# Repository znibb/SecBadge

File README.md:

View this project on [CADLAB.io](https://cadlab.io/node/992). 

# SecBadge

Board dimensions: 69x43 mm

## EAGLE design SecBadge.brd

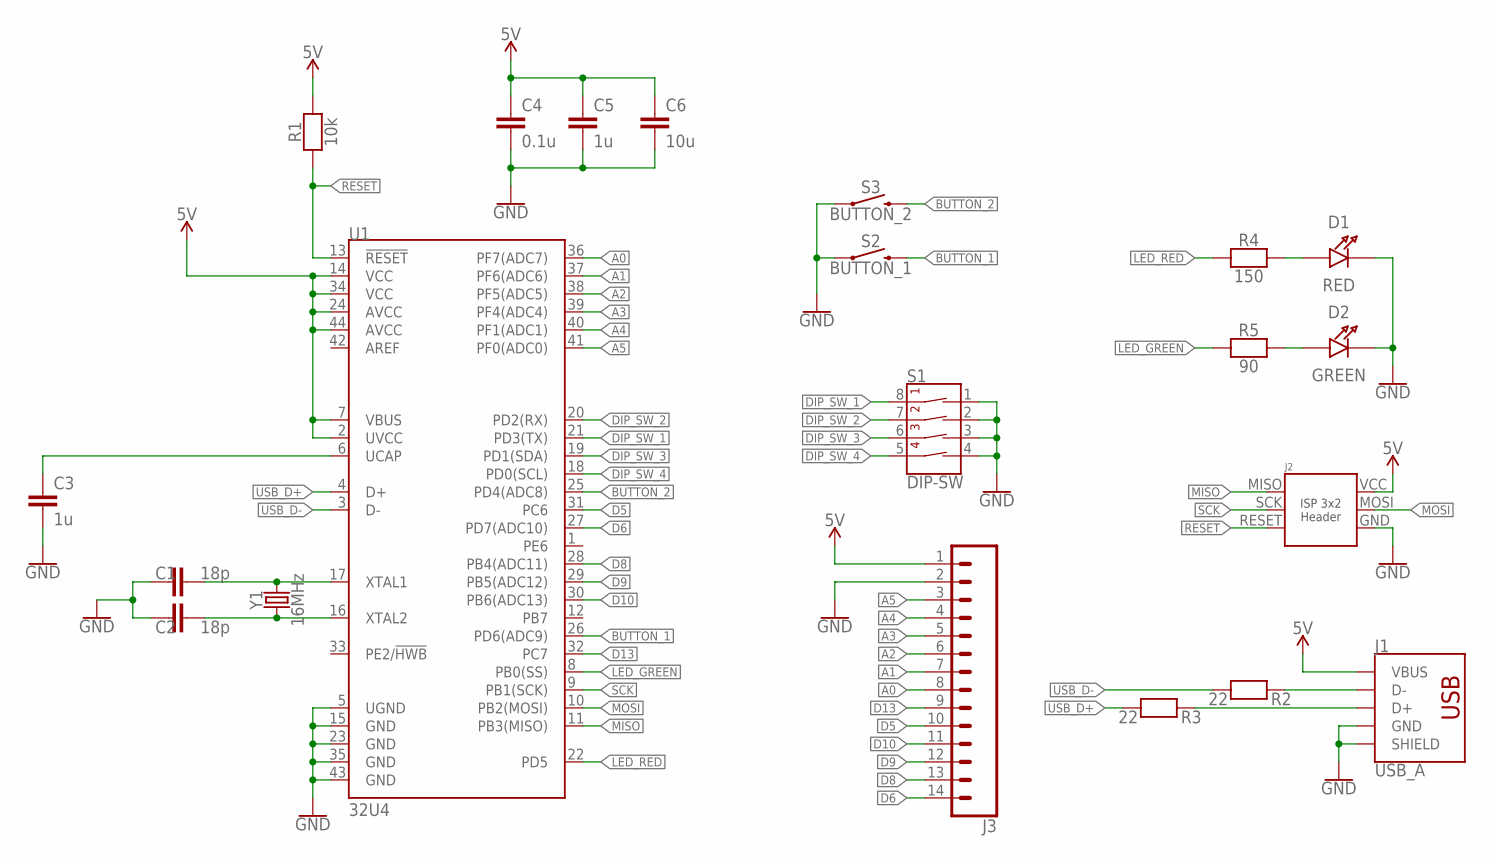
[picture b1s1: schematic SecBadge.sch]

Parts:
C1, C2: 18p; 1206
C3, C5: 1u; 1206
C4: 0.1u; 1206
C6: 10u; 1206
D1: RED; LED-1206
D2: GREEN; LED-1206
J1: USB_A; USB_A_MALE_THT
J2: AVR_ISP_PROG_3X2; 3X2_NO_SILK
J3: CONN_14; 1X14
R1: 10k; 1206
R2, R3: 22; 1206
R4: 150; 1206
R5: 90; 1206
S1: DIP-SW; DIP8
S2: BUTTON_1; TACTILE_SWITCH_PTH_6.0MM
S3: BUTTON_2; TACTILE_SWITCH_PTH_6.0MM
U1: 32U4; TQFP44
Y1: 16MHz; HC49UP

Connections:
5V: C4.1, C5.1, C6.1, J1.VBUS, J2.VCC, J3.1, R1.1, U1.2 (UVCC), U1.7 (VBUS), U1.14 (VCC), U1.24 (AVCC), U1.34 (VCC), U1.44 (AVCC)
A0: J3.8, U1.36 (PF7(ADC7))
A1: J3.7, U1.37 (PF6(ADC6))
A2: J3.6, U1.38 (PF5(ADC5))
A3: J3.5, U1.39 (PF4(ADC4))
A4: J3.4, U1.40 (PF1(ADC1))
A5: J3.3, U1.41 (PF0(ADC0))
BUTTON_1: S2.3 (2), U1.26 (PD6(ADC9))
BUTTON_2: S3.3 (2), U1.25 (PD4(ADC8))
D5: J3.10, U1.31 (PC6)
D6: J3.14, U1.27 (PD7(ADC10))
D8: J3.13, U1.28 (PB4(ADC11))
D9: J3.12, U1.29 (PB5(ADC12))
D10: J3.11, U1.30 (PB6(ADC13))
D13: J3.9, U1.32 (PC7)
DIP_SW_1: S1.8 (1B), U1.21 (PD3(TX))
DIP_SW_2: S1.7 (2B), U1.20 (PD2(RX))
DIP_SW_3: S1.6 (3B), U1.19 (PD1(SDA))
DIP_SW_4: S1.5 (4B), U1.18 (PD0(SCL))
GND: C1.1, C2.1, C3.2, C4.2, C5.2, C6.2, D1.C (CATHODE), D2.C (CATHODE), J1.GND, J1.SHIELD1 (SHIELD), J1.SHIELD2 (SHIELD), J2.GND, J3.2, S1.1 (1A), S1.2 (2A), S1.3 (3A), S1.4 (4A), S2.1, S3.1, U1.5 (UGND), U1.15 (GND), U1.23 (GND), U1.35 (GND), U1.43 (GND)
LED_GREEN: R5.2, U1.8 (PB0(SS))
LED_RED: R4.2, U1.22 (PD5)
MISO: J2.MISO, U1.11 (PB3(MISO))
MOSI: J2.MOSI, U1.10 (PB2(MOSI))
unnamed: C1.2, U1.17 (XTAL1), Y1.2
unnamed: J1.D-, R2.2
unnamed: J1.D+, R3.2
unnamed: C2.2, U1.16 (XTAL2), Y1.1
unnamed: C3.1, U1.6 (UCAP)
unnamed: D1.A (ANODE), R4.1
unnamed: D2.A (ANODE), R5.1
RESET: J2.RESET, R1.2, U1.13 (!RESET)
SCK: J2.SCK, U1.9 (PB1(SCK))
USB_D+: R3.1, U1.4 (D+)
USB_D-: R2.1, U1.3 (D-)

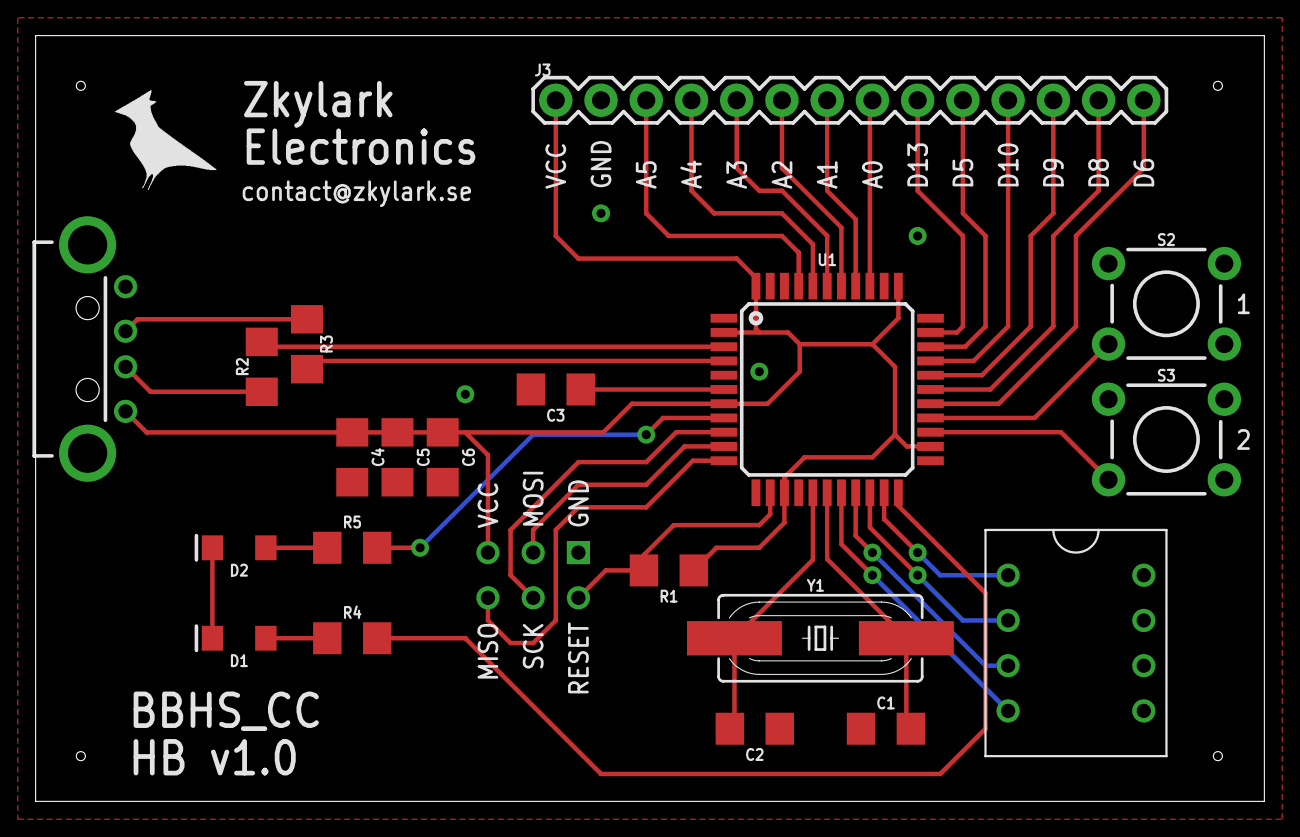
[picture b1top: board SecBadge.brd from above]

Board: 2 copper layers, 69.0 x 43.0 mm, 21 parts (0 on the bottom side), 35 nets.

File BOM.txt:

Partlist exported from C:/Users/znibb/Dropbox/Eagle_7.6/projects/SecBadge/SecBadge.sch at 01/04/2018 13:42

Part Value  Device                          Package                  Description          PROD_ID     SF_SKU    VALUE
C1   18p    CAPACITOR1206                   1206                                                                     
C2   18p    CAPACITOR1206                   1206                                                                     
C3   1u     CAPACITOR1206                   1206                                                                     
C4   0.1u   CAPACITOR1206                   1206                                                                     
C5   1u     CAPACITOR1206                   1206                                                                     
C6   10u    CAPACITOR1206                   1206                                                                     
D1   RED    LED                             LED-1206                                                                 
D2   GREEN  LED                             LED-1206                                                                 
J1   USB_A  USB_A                           USB_A_MALE_THT           USB-A Connector                                 
J2          AVR_ISP_PROG_3X2                3X2_NO_SILK              ISP Header                                      
R1   10k    RESISTOR1206                    1206                                                                     
R2   22     RESISTOR1206                    1206                                                                     
R3   22     RESISTOR1206                    1206                                                                     
R4   150    RESISTOR1206                    1206                                                                     
R5   90     RESISTOR1206                    1206                                                                     
S1   DIP-SW DIP-SW-4POSPHT                  DIP8                     4-Position DIP Switc                            
S2          MOMENTARY-SWITCH-SPST-PTH-6.0MM TACTILE_SWITCH_PTH_6.0MM Momentary Switch (Pu  SWCH-08441 COM-00097      
S3          MOMENTARY-SWITCH-SPST-PTH-6.0MM TACTILE_SWITCH_PTH_6.0MM Momentary Switch (Pu  SWCH-08441 COM-00097      
U1   32U4   ATMEGA32U4TQFP-44               TQFP44                   Atmel MCU, 32KByte   IC-11161              32U4 
Y1   16MHz  CRYSTALSMD-HC49UP               HC49UP                   Crystals (Generic)

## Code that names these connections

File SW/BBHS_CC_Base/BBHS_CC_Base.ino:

/*
Base sketch for the Bug Bounty Hunters Sweden Challenge Card.
Button 1 turns on the green LED for a set amount of time, DIP1&2 doubles the on-time respectively.
Button 2 turns on the red LED for a set amount of time, DIP3&4 doubles the on-time respectively.

Known issue: Clock rollover after 49 days runtime will make LEDs turn on "for good", deal with it.
*/

// DIP switches: 1-PD3, 2-PD2, 3-PD1, 4-PD0
// Buttons: 1-PD6-D12, 2-PD4-D4
// LEDs: Green-PB0, Red-PD5

// For explanation of port manipulation see: https://www.arduino.cc/en/Reference/PortManipulation

#include <Bounce2.h>  // Used for bounce-free buttons

// Bit masks for each feature
#define DIP1 B00001000
#define DIP2 B00000100
#define DIP3 B00000010
#define DIP4 B00000001
#define BUTTON1 B01000000
#define BUTTON2 B00010000
#define LED_GREEN B00000001
#define LED_RED B00100000

// Debouncer objects
Bounce bouncer1 = Bounce();
Bounce bouncer2 = Bounce();

// Function declarations
bool getButton(byte);
bool getDIP(byte);
void setLED(byte, bool);

// Parameters
const byte debounceInterval = 20;
const int baseLedOnTime = 1000;

// Variables
bool ledGreenState = false;
bool ledRedState = false;
unsigned long ledGreenOffTime = 0;
unsigned long ledRedOffTime = 0;

void setup() {  
  // DIP switches
  DDRD &=  ~(DIP1 | DIP2 | DIP3 | DIP4);  // Set as inputs
  PORTD |=  (DIP1 | DIP2 | DIP3 | DIP4);  // Activate input pullups

  // Buttons
  DDRD &=  ~(BUTTON1 | BUTTON2);        // Set Button 1&2 as inputs
  PORTD |=  (BUTTON1 | BUTTON2);        // Activate input pullups
  bouncer1.attach(12);                  // Attach debouncer to button 1
  bouncer1.interval(debounceInterval);  // Set debounce deadzone
  bouncer2.attach(4);                   // Attach debouncer to button 2
  bouncer2.interval(debounceInterval);  // Set debounce deadzone

  // LEDs
  DDRB |=   LED_GREEN;  // Set Green LED as output
  PORTB &= ~LED_GREEN;  // Set Green LED default low
  DDRD |=   LED_RED;    // Set Red LED as output
  PORTD &= ~LED_RED;    // Set Red LED default low
}

void loop() {
  // Update bouncers
  bouncer1.update();
  bouncer2.update();
  
  // If button 1 was pressed, turn on green LED
  if(bouncer1.fell() == HIGH){
    setLED(1, HIGH);
    ledGreenState = true;
    int duration = baseLedOnTime;

    // Double the LED on time for each of DIP1&2 that is ON (bit shift left <=> multiply by 2)
    if(getDIP(1) == LOW){
      duration = duration << 1;
    }
    if(getDIP(2) == LOW){
      duration =  duration << 1;
    }

    // Set planned time to turn off
    ledGreenOffTime = millis() + duration;    
  }

  // If button 2 was pressed, turn on red LED
  if(bouncer2.fell() == HIGH){
    setLED(2, HIGH);
    ledRedState = true;
    int duration = baseLedOnTime;

    // Double the LED on time for each of DIP3&4 that is ON (bit shift left <=> multiply by 2)
    if(getDIP(3) == LOW){
      duration = duration << 1;
    }
    if(getDIP(4) == LOW){
      duration =  duration << 1;
    }

    // Set planned time to turn off
    ledRedOffTime = millis() + duration;    
  }

  // Check if LEDs are due to turn off
  if(ledGreenState){  // If Green LED is lit
    if(millis() >= ledGreenOffTime){
      setLED(1, false);
      ledGreenState = false;
    }
  }
  if(ledRedState){  // If Red LED is lit
    if(millis() >= ledRedOffTime){
      setLED(2, false);
      ledRedState = false;
    }
  }
}

// Returns the state of buttons 1 and 2, LOW = button pressed
bool getButton(byte i){
  switch(i){
    case 1:
      return PIND &= BUTTON1;
    case 2:
      return PIND &= BUTTON2;
    default:
      return false;
  }
}

// Returns the state of DIP switch 1-4, LOW = ON
bool getDIP(byte i){
  switch(i){
    case 1:
      return PIND &= DIP1;
    case 2:
      return PIND &= DIP2;
    case 3:
      return PIND &= DIP3;
    case 4:
      return PIND &= DIP4;
    default:
      return false;
  }
}

// Sets the state of LED 1&2 (green&red), HIGH = ON
void setLED(byte i, bool value){
  switch(i){
    case 1: // Green LED
      if(value == HIGH){
        PORTB |= LED_GREEN;
      }
      else {
        PORTB &= ~LED_GREEN;
      }
      break;
    case 2: // Red LED
      if(value == HIGH){
        PORTD |= LED_RED;
      }
      else{
        PORTD &= ~LED_RED;
      }
      break;
    default:
      break;
  }
}

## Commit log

2018-04-01 Initial draft of Mk1 design.
2018-04-01 Added button designator in schematic.
2018-04-02 Added logotype import script
2018-04-02 Added VCC and GND to expansion header.
2018-04-02 Gerber files for final draft of v1.0.
2018-04-03 Removed logotype import script.
2018-04-03 Updated board silkscreen info.
2018-04-03 Final gerbers for v1.0.
2018-04-03 Added board dimensions.
2018-05-07 Backlink to CADLAB.io has been added.
2018-05-25 Added base sketch that demos the boards capabilities.
2018-05-25 Added README
2018-05-25 Updated formatting of README
2018-05-25 Updated README
    Added directions on how to install Bounce2 library.
2018-05-25 Update README
    Added tested library version.
2018-05-25 Fixed LED persistantly on
    Changed time keeping variables from int to unsigned long to prevent
    rollover.

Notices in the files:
parts and their libraries:
SparkFun-Switches: Licensing: Creative Commons ShareAlike 4.0 International - https://creativecommons.org/licenses/by-sa/4.0
